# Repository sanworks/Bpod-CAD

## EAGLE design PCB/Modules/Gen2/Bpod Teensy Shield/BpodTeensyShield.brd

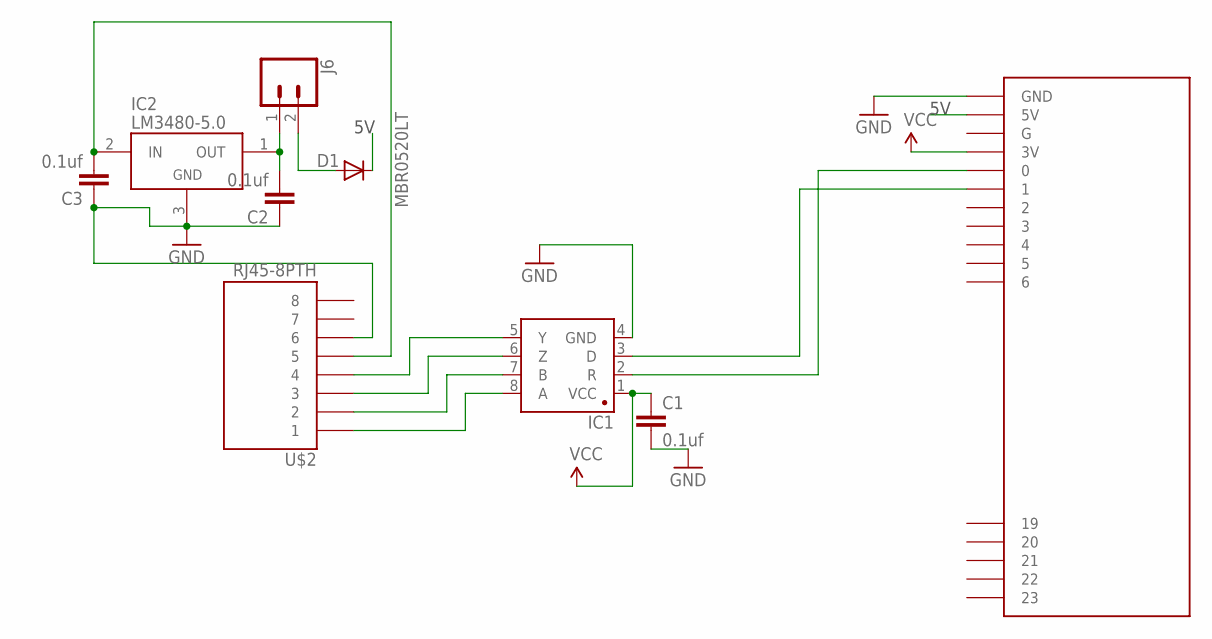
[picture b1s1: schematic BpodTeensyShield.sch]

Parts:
C1, C2, C3: 0.1uf; 1206@1
D1: MBR0520LT; SOD123
IC1: SN65HVD31DR; SO08
IC2: LM3480-5.0; SOT-23-3
J6: CONN_02; 1X02
U$1: AUDIOSHIELD
U$2: RJ45-8PTH; RJ45-8

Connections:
5V: D1.C, U$1.5V
GND: C1.2, C2.1, C3.1, IC1.4 (GND), IC2.3 (GND), U$1.GND, U$2.6
unnamed: IC1.8 (A), U$2.1
unnamed: IC1.7 (B), U$2.2
unnamed: IC1.6 (Z), U$2.3
unnamed: IC1.5 (Y), U$2.4
unnamed: C2.2, IC2.1 (OUT), J6.1
unnamed: D1.A, J6.2
unnamed: C3.2, IC2.2 (IN), U$2.5
RX1: IC1.2 (R), U$1.0
TX1: IC1.3 (D), U$1.1
VCC: C1.1, IC1.1 (VCC), U$1.3V

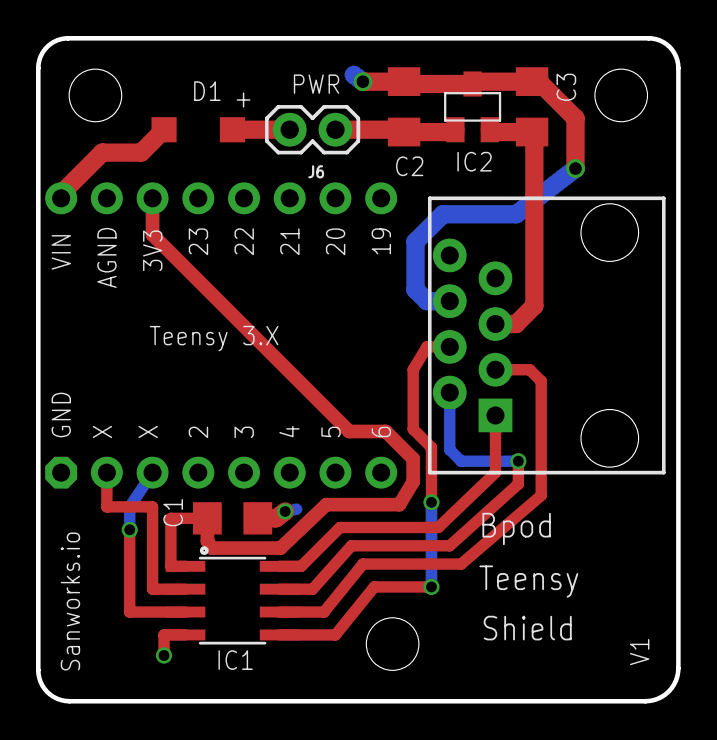
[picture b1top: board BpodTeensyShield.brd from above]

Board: 2 copper layers, 35.6 x 36.8 mm, 9 parts (0 on the bottom side), 12 nets.

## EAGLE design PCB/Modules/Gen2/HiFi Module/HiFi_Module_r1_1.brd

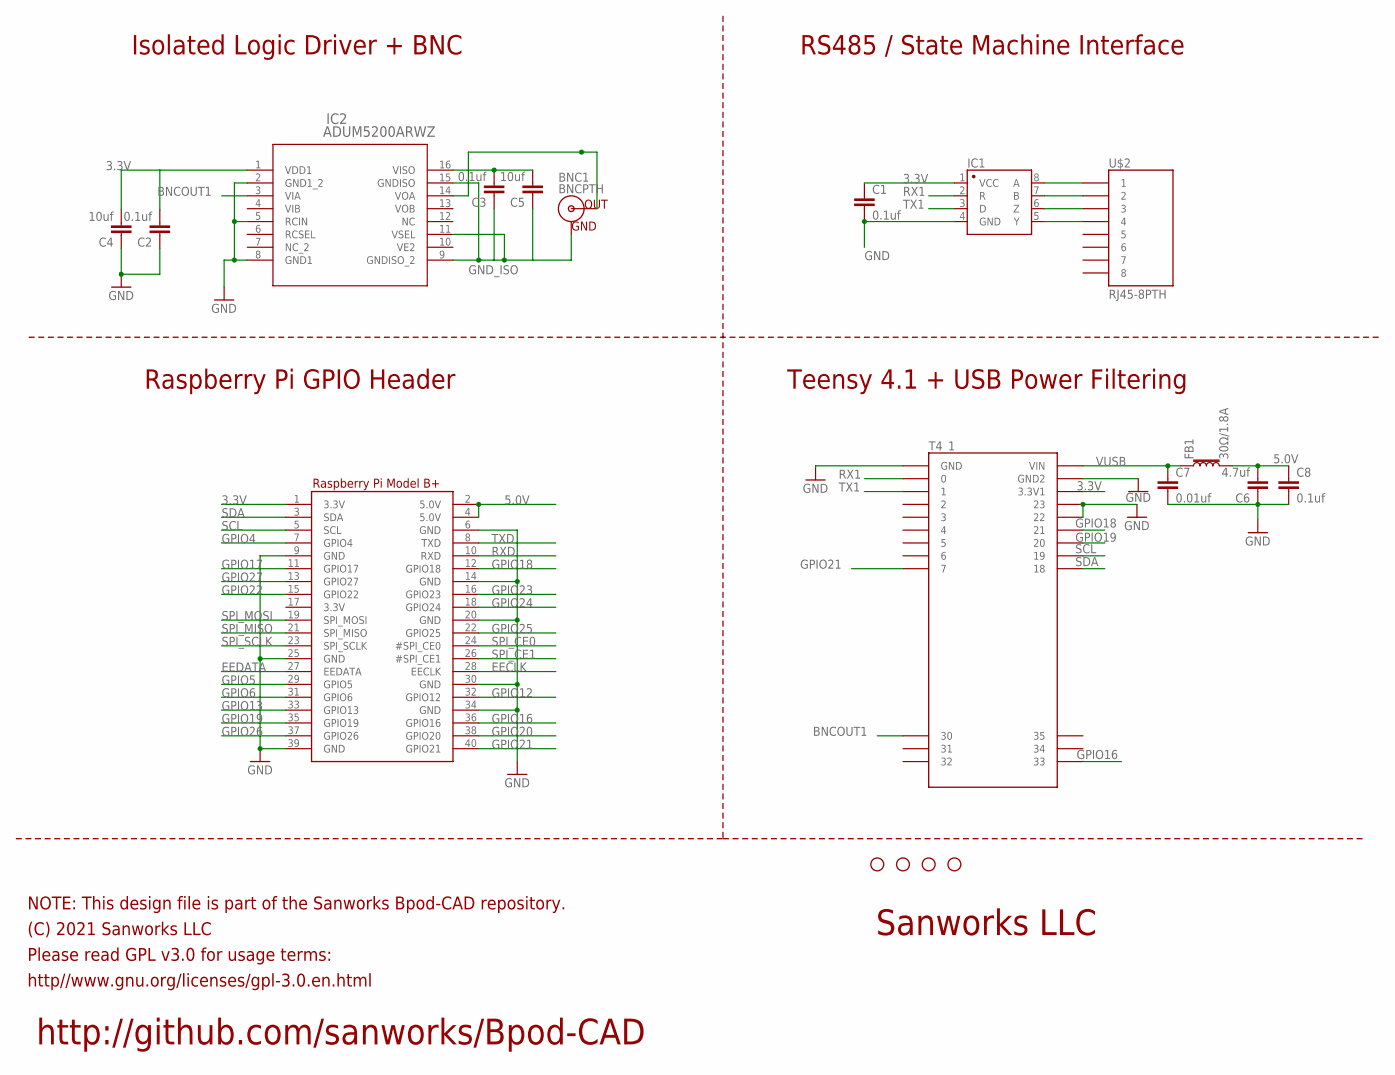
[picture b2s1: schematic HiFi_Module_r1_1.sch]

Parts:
BNC1: BNCPTH; BNC
C1, C2, C3, C8: 0.1uf; 0805
C4, C5: 10uf; 1206@2
C6: 4.7uf; 1206@2
C7: 0.01uf; 0805
FB1: 30Ω/1.8A; 0603
H1, H2, H3, H4: STAND-OFF
IC1: SN65HVD31DR; SO08
IC2: ADUM5200ARWZ; RW_16
RPI1: RASPBERRYPI_BPLUS_IDC; 2X20
T4_1: TEENSY4.1_FORAUDIO
U$2: RJ45-8PTH; RJ45-8

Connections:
3.3V: C1.1, C2.2, C4.2, IC1.1 (VCC), IC2.1 (VDD1), RPI1.1 (3.3V), T4_1.3V3_LO (3.3V1)
5.0V: C6.2, C8.1, FB1.2, RPI1.2 (5.0V), RPI1.4 (5.0V)
BNCOUT1: IC2.3 (VIA), T4_1.30
EECLK: RPI1.28 (EECLK)
EEDATA: RPI1.27 (EEDATA)
GND: C1.2, C2.1, C4.1, C6.1, C7.2, C8.2, IC1.4 (GND), IC2.2 (GND1_2), IC2.5 (RCIN), IC2.8 (GND1), RPI1.6 (GND), RPI1.9 (GND), RPI1.14 (GND), RPI1.20 (GND), RPI1.25 (GND), RPI1.30 (GND), RPI1.34 (GND), RPI1.39 (GND), T4_1.22/A8 (22), T4_1.23/A9 (23), T4_1.AGND (GND), T4_1.GND (GND2)
GND_ISO: BNC1.GND, C3.1, C5.1, IC2.9 (GNDISO_2), IC2.11 (VSEL), IC2.15 (GNDISO)
GPIO4: RPI1.7 (GPIO4)
GPIO5: RPI1.29 (GPIO5)
GPIO6: RPI1.31 (GPIO6)
GPIO12: RPI1.32 (GPIO12)
GPIO13: RPI1.33 (GPIO13)
GPIO16: RPI1.36 (GPIO16), T4_1.33
GPIO17: RPI1.11 (GPIO17)
GPIO18: RPI1.12 (GPIO18), T4_1.21/A7 (21)
GPIO19: RPI1.35 (GPIO19), T4_1.20/A6 (20)
GPIO20: RPI1.38 (GPIO20)
GPIO21: RPI1.40 (GPIO21), T4_1.7
GPIO22: RPI1.15 (GPIO22)
GPIO23: RPI1.16 (GPIO23)
GPIO24: RPI1.18 (GPIO24)
GPIO25: RPI1.22 (GPIO25)
GPIO26: RPI1.37 (GPIO26)
GPIO27: RPI1.13 (GPIO27)
unnamed: IC1.6 (Z), U$2.3
unnamed: IC1.8 (A), U$2.1
unnamed: IC1.5 (Y), U$2.4
unnamed: IC1.7 (B), U$2.2
unnamed: C3.2, C5.2, IC2.16 (VISO)
unnamed: BNC1.S (OUT), IC2.14 (VOA)
RX1: IC1.2 (R), T4_1.0/RX (0)
RXD: RPI1.10 (RXD)
SCL: RPI1.5 (SCL), T4_1.19/A5/SCL (19)
SDA: RPI1.3 (SDA), T4_1.18/A4/SDA (18)
SPI_CE0: RPI1.24 (#SPI_CE0)
SPI_CE1: RPI1.26 (#SPI_CE1)
SPI_MISO: RPI1.21 (SPI_MISO)
SPI_MOSI: RPI1.19 (SPI_MOSI)
SPI_SCLK: RPI1.23 (SPI_SCLK)
TX1: IC1.3 (D), T4_1.1/TX (1)
TXD: RPI1.8 (TXD)
VUSB: C7.1, FB1.1, T4_1.VIN

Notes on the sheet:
http://github.com/sanworks/Bpod-CAD
NOTE: This design file is part of the Sanworks Bpod-CAD repository.
(C) 2021 Sanworks LLC
http//www.gnu.org/licenses/gpl-3.0.en.html
Please read GPL v3.0 for usage terms:
Sanworks LLC
Isolated Logic Driver + BNC
RS485 / State Machine Interface
Raspberry Pi GPIO Header
Teensy 4.1 + USB Power Filtering

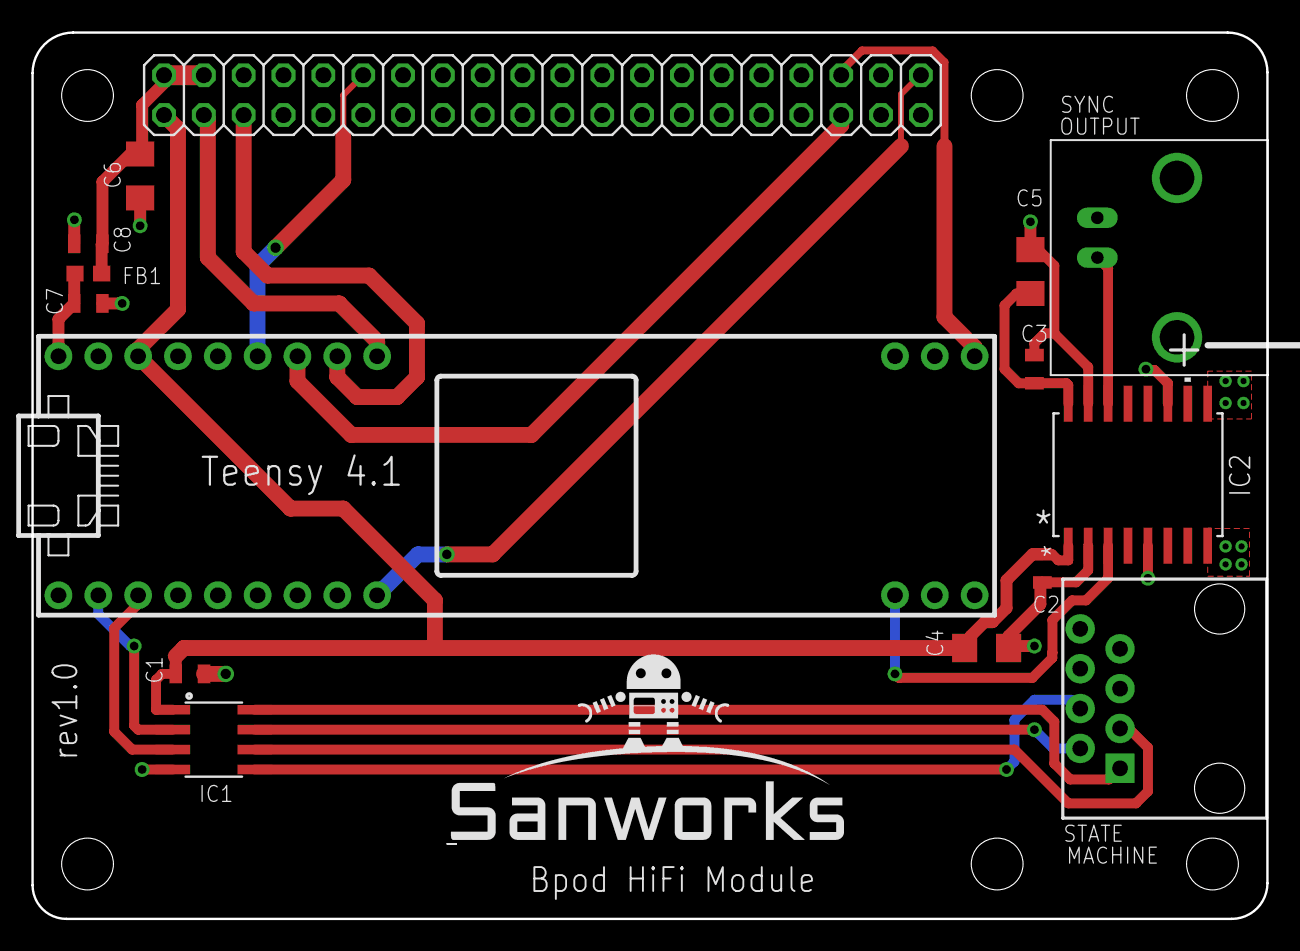
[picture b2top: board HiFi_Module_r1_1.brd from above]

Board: 2 copper layers, 78.7 x 56.5 mm, 22 parts (0 on the bottom side), 20 nets.

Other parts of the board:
H5, H6: STAND-OFF
U$1: SANWORKS_LOGO

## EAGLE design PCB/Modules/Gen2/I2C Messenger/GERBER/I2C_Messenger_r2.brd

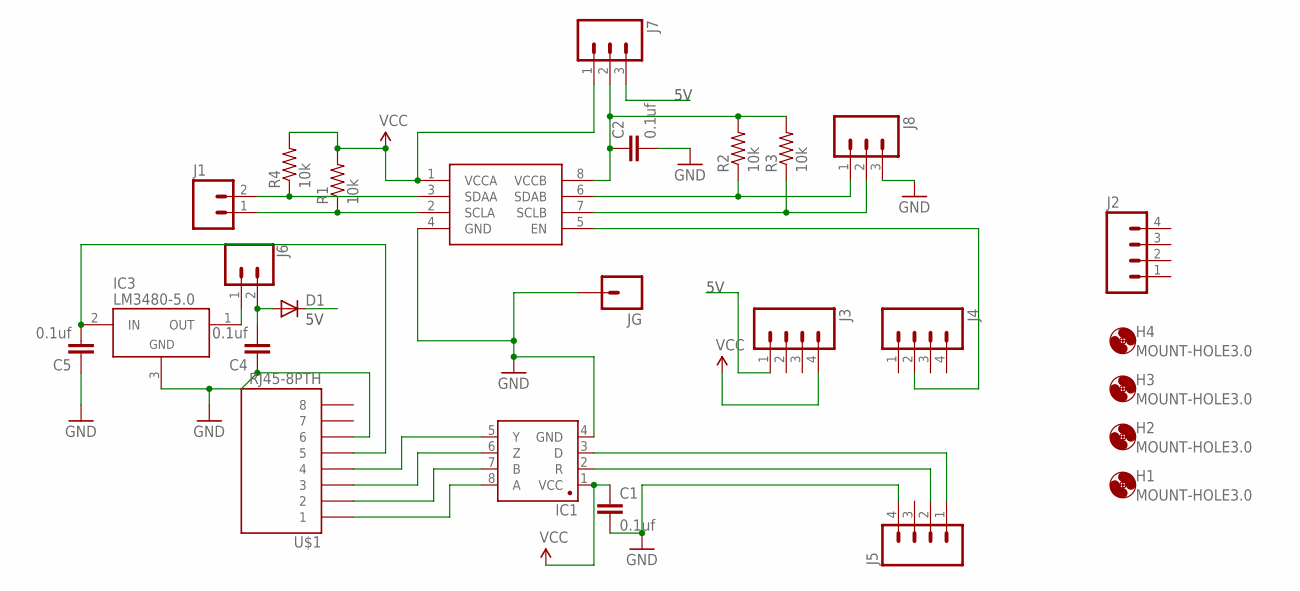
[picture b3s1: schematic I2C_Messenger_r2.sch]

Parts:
C1, C2, C4, C5: 0.1uf; 1206
D1: MBR0520LT; SOD123
H1, H2, H3, H4: MOUNT-HOLE3.0; 3,0
IC1: SN65HVD31DR; SO08
IC2: PCA9517; SO-08
IC3: LM3480-5.0; SOT-23-3
J1: M02PTH; 1X02@1
J2, J3, J4, J5: M04PTH; 1X04
J6: CONN_02; 1X02
J7: M03PTH; 1X03
J8: M03SCREW_LOCK; SCREWTERMINAL-3.5MM-3_LOCK.007S
JG: M01PTH; 1X01
R1, R2, R3, R4: 10k; 1206
U$1: RJ45-8PTH; RJ45-8

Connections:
5V: D1.C, J3.1, J7.3
GND: C1.2, C2.2, C4.1, C5.1, IC1.4 (GND), IC2.4 (GND), IC3.3 (GND), J5.4, J8.3, JG.1, U$1.6
unnamed: C4.2, D1.A, J6.2
unnamed: IC3.1 (OUT), J6.1
unnamed: IC1.3 (D), J5.1
unnamed: IC2.2 (SCLA), J1.1, R1.1
unnamed: IC1.2 (R), J5.2
unnamed: IC1.8 (A), U$1.1
unnamed: IC1.7 (B), U$1.2
unnamed: IC1.6 (Z), U$1.3
unnamed: IC1.5 (Y), U$1.4
unnamed: IC2.3 (SDAA), J1.2, R4.1
unnamed: C2.1, IC2.8 (VCCB), J7.2, R2.2, R3.2
unnamed: IC2.5 (EN), J4.2
unnamed: IC2.6 (SDAB), J8.1, R2.1
unnamed: IC2.7 (SCLB), J8.2, R3.1
unnamed: C5.2, IC3.2 (IN), U$1.5
VCC: C1.1, IC1.1 (VCC), IC2.1 (VCCA), J3.4, J7.1, R1.2, R4.2

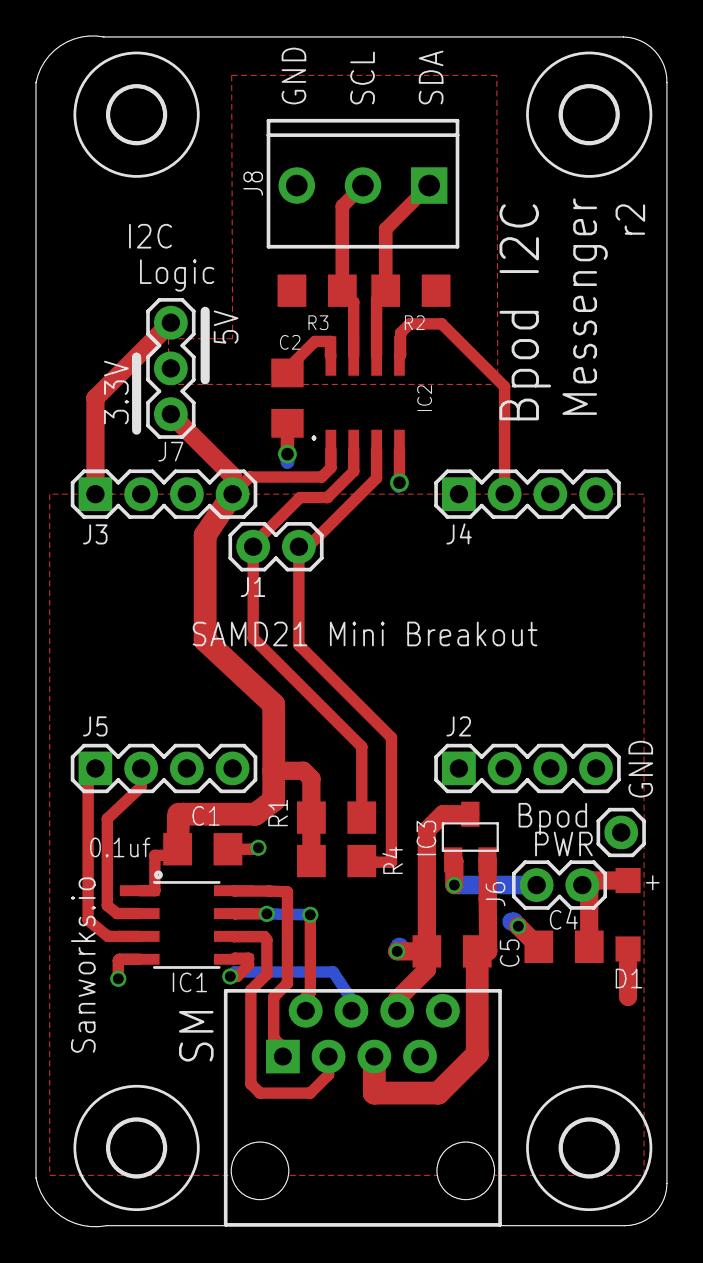
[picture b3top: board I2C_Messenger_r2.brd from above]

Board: 2 copper layers, 35.1 x 66.1 mm, 26 parts (0 on the bottom side), 18 nets.

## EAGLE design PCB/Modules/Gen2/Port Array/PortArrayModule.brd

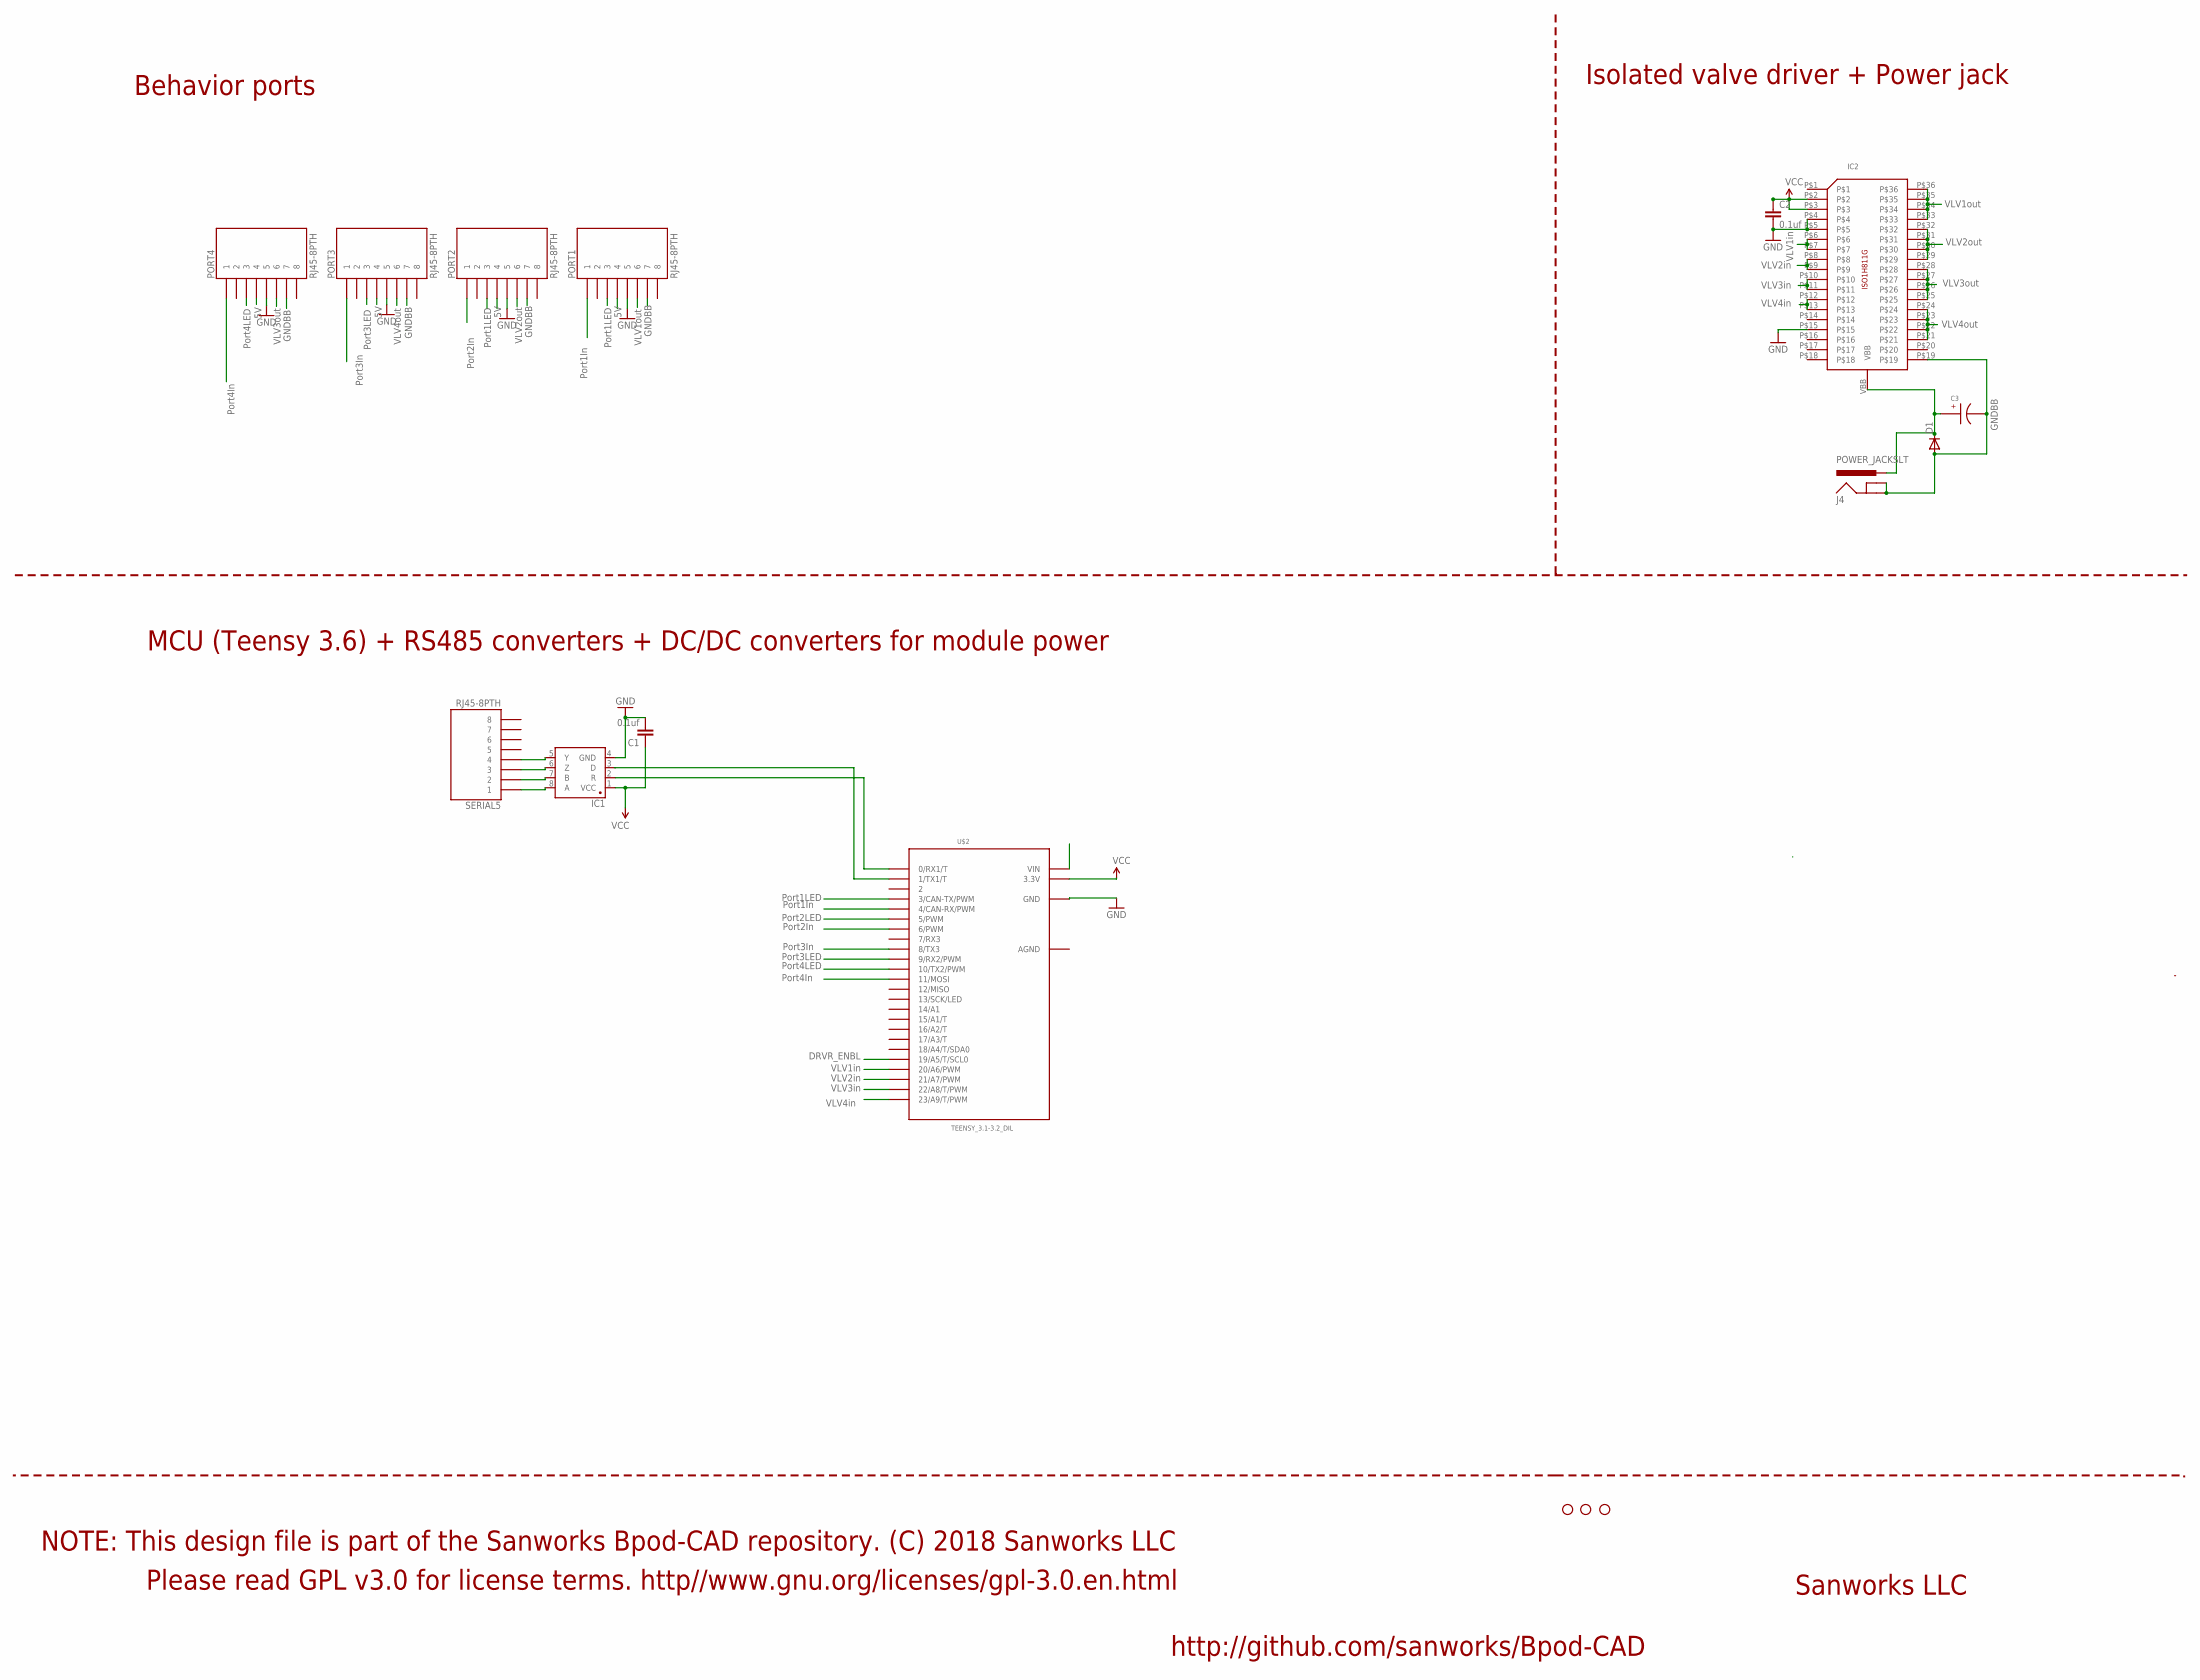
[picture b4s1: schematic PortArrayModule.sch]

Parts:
C1, C2: 0.1uf; 1206@1
C3: EEE-FK1H100UR
D1: DIODE-DO214AA; DO214AA
IC1: SN65HVD31DR; SO08
IC2: ISO1H811G
J4: POWER_JACKSLT; POWER_JACK_SLOT
JP3, JP4, JP5: STAND-OFF
PORT1, PORT2, PORT3, PORT4: RJ45-8PTH; RJ45-8
SERIAL5: RJ45-8PTH; RJ45-8
U$2: TEENSY_3.1-3.2_DIL; TEENSY_3.0-3.2&LC_DIL

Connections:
5V: PORT1.4, PORT2.4, PORT3.4, PORT4.4, U$2.VIN
AGND: U$2.AGND
DRVR_ENBL: U$2.19/A5 (19/A5/T/SCL0)
GND: C1.2, C2.2, IC1.4 (GND), IC2.P$4, IC2.P$5, IC2.P$15, PORT1.5, PORT2.5, PORT3.5, PORT4.5, U$2.GND
GNDBB: C3.CATHODE, D1.A, IC2.P$19, J4.GND@1 (GNDBREAK), J4.GND@2 (GND), PORT1.7, PORT2.7, PORT3.7, PORT4.7
unnamed: IC1.8 (A), SERIAL5.1
unnamed: IC1.7 (B), SERIAL5.2
unnamed: IC1.6 (Z), SERIAL5.3
unnamed: IC1.5 (Y), SERIAL5.4
unnamed: IC1.3 (D), U$2.1 (1/TX1/T)
unnamed: IC1.2 (R), U$2.0 (0/RX1/T)
PORT1IN: PORT1.1, U$2.4 (4/CAN-RX/PWM)
PORT1LED: PORT1.3, U$2.3 (3/CAN-TX/PWM)
PORT2IN: PORT2.1, U$2.6 (6/PWM)
PORT2LED: PORT2.3, U$2.5 (5/PWM)
PORT3IN: PORT3.1, U$2.8 (8/TX3)
PORT3LED: PORT3.3, U$2.9 (9/RX2/PWM)
PORT4IN: PORT4.1, U$2.11 (11/MOSI)
PORT4LED: PORT4.3, U$2.10 (10/TX2/PWM)
VBB: C3.ANODE, D1.C, IC2.VBB, J4.PWR
VCC: C1.1, C2.1, IC1.1 (VCC), IC2.P$2, IC2.P$3, U$2.3.3V
VLV1IN: IC2.P$6, IC2.P$7, U$2.20/A6 (20/A6/PWM)
VLV1OUT: IC2.P$33, IC2.P$34, IC2.P$35, IC2.P$36, PORT1.6
VLV2IN: IC2.P$8, IC2.P$9, U$2.21/A7 (21/A7/PWM)
VLV2OUT: IC2.P$29, IC2.P$30, IC2.P$31, IC2.P$32, PORT2.6
VLV3IN: IC2.P$12, IC2.P$13, U$2.23/A9 (23/A9/T/PWM)
VLV3OUT: IC2.P$21, IC2.P$22, IC2.P$23, IC2.P$24, PORT3.6
VLV4IN: IC2.P$10, IC2.P$11, U$2.22/A8 (22/A8/T/PWM)
VLV4OUT: IC2.P$25, IC2.P$26, IC2.P$27, IC2.P$28, PORT4.6

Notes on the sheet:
Port1In
Port2In
Port3In
Port4In
Port1LED
Port2LED
Port3LED
Port4LED
DRVR_ENBL
VLV2in
VLV3in
VLV4in
VLV1in
GNDBB
VLV1out
VLV2out
VLV3out
VLV4out
Sanworks LLC
http://github.com/sanworks/Bpod-CAD
Please read GPL v3.0 for license terms. http//www.gnu.org/licenses/gpl-3.0.en.html
NOTE: This design file is part of the Sanworks Bpod-CAD repository. (C) 2018 Sanworks LLC
Behavior ports
Isolated valve driver + Power jack
MCU (Teensy 3.6) + RS485 converters + DC/DC converters for module power

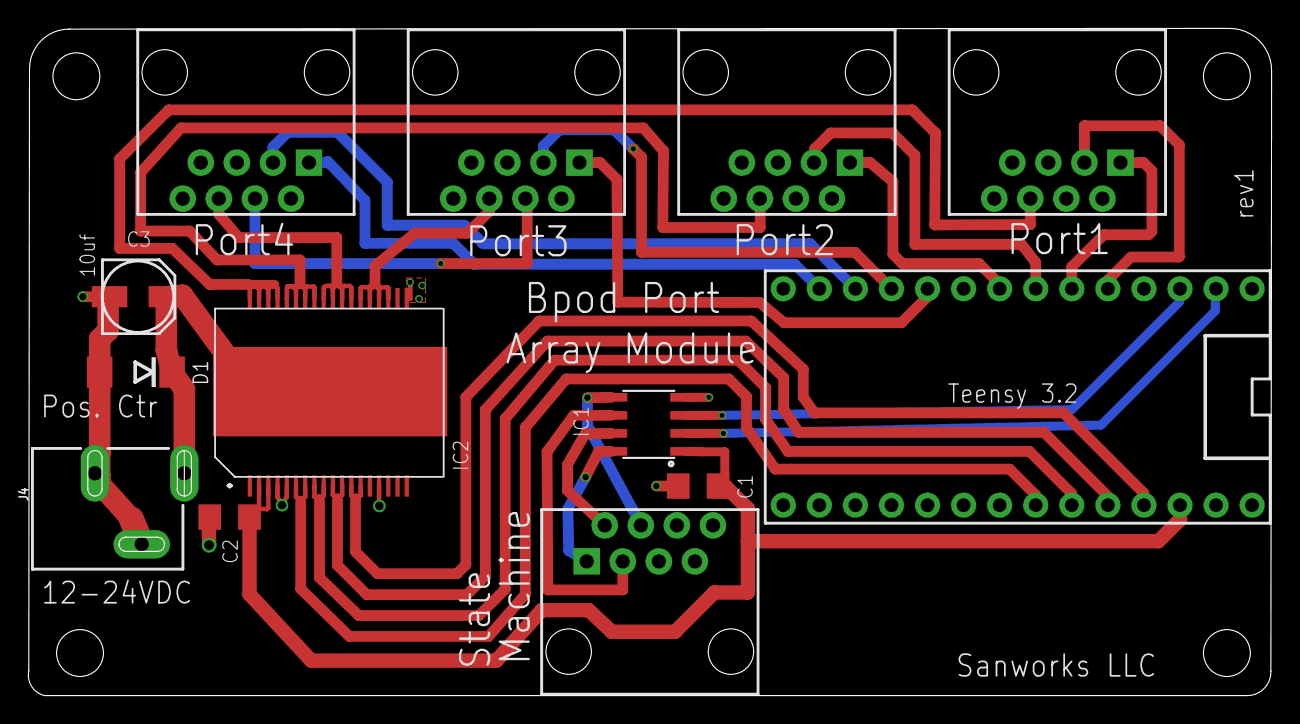
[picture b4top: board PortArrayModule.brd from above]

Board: 4 copper layers, 87.6 x 47.0 mm, 17 parts (0 on the bottom side), 27 nets.

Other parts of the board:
JP1: STAND-OFF

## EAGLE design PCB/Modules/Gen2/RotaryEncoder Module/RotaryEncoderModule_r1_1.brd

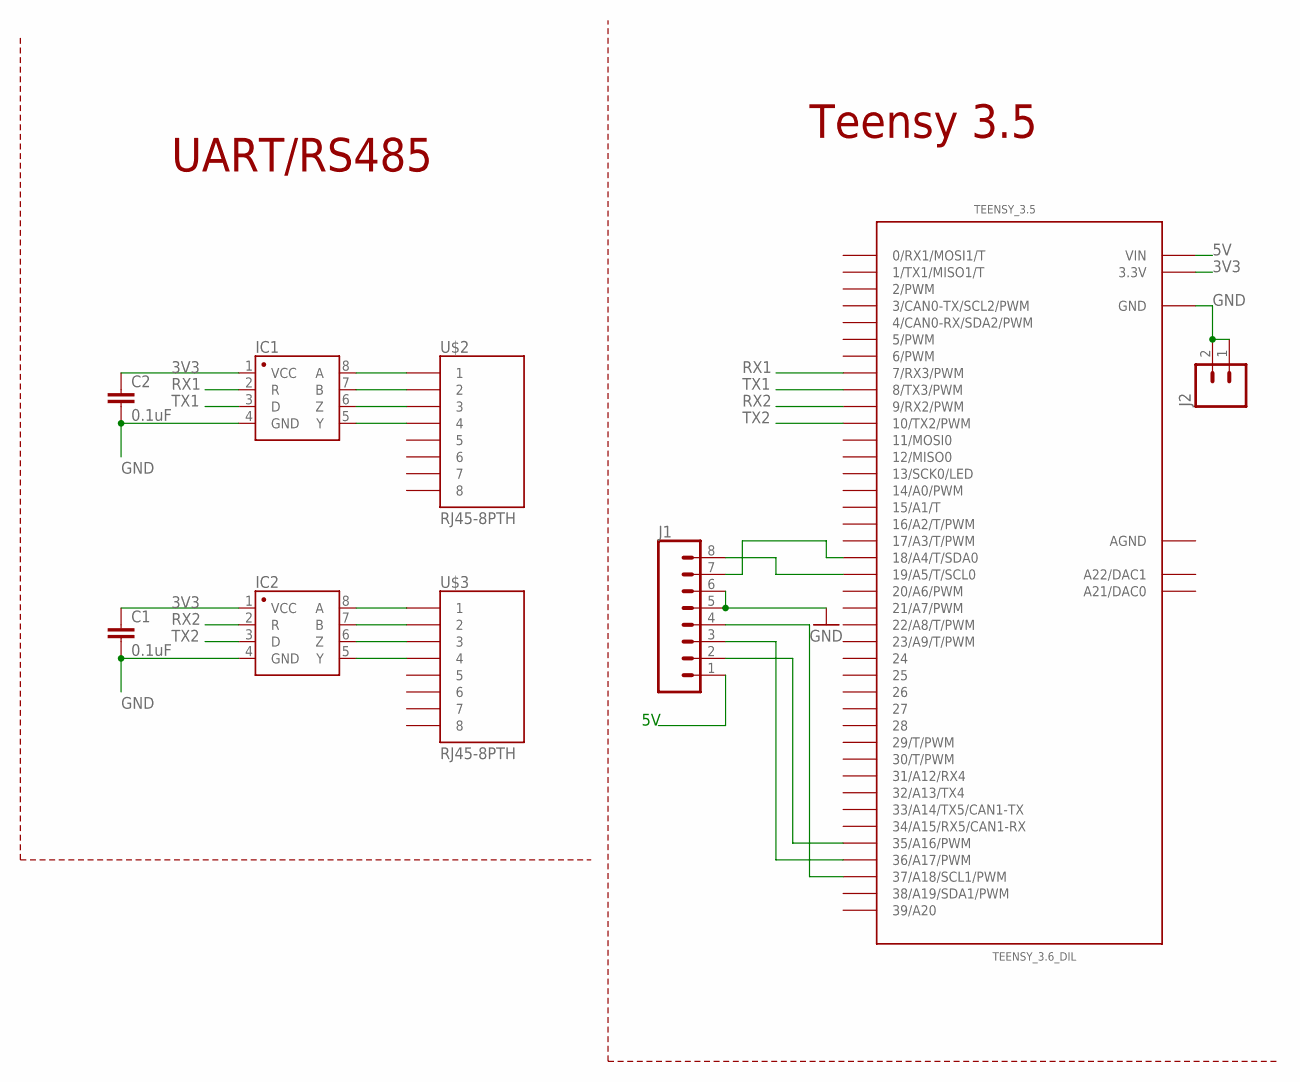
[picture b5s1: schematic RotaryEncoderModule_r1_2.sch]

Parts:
C1, C2: 0.1uF; 1206
IC1, IC2: SN65HVD31DR; SO08
J1: CONN_083.5MM-8; SCREWTERMINAL-3.5MM-8
J2: M023.5MM; SCREWTERMINAL-3.5MM-2
TEENSY_3.5: TEENSY_3.6_DIL
U$2, U$3: RJ45-8PTH; RJ45-8

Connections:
3V3: C1.1, C2.1, IC1.1 (VCC), IC2.1 (VCC), TEENSY_3.5.3.3V, TEENSY_3.5.3.3V3 (3.3V)
5V: J1.1, TEENSY_3.5.VIN
AGND: TEENSY_3.5.AGND
GND: C1.2, C2.2, IC1.4 (GND), IC2.4 (GND), J1.5, J1.6, J2.1, J2.2, TEENSY_3.5.GND, TEENSY_3.5.GND1 (GND)
unnamed: IC1.6 (Z), U$2.3
unnamed: IC1.8 (A), U$2.1
unnamed: IC1.5 (Y), U$2.4
unnamed: IC1.7 (B), U$2.2
unnamed: IC2.6 (Z), U$3.3
unnamed: IC2.5 (Y), U$3.4
unnamed: IC2.8 (A), U$3.1
unnamed: IC2.7 (B), U$3.2
unnamed: J1.8, TEENSY_3.5.19/A5 (19/A5/T/SCL0)
unnamed: J1.7, TEENSY_3.5.18/A4 (18/A4/T/SDA0)
unnamed: J1.2, TEENSY_3.5.35/A16 (35/A16/PWM)
unnamed: J1.3, TEENSY_3.5.36/A17 (36/A17/PWM)
unnamed: J1.4, TEENSY_3.5.37/A18 (37/A18/SCL1/PWM)
RX1: IC1.2 (R), TEENSY_3.5.7 (7/RX3/PWM)
RX2: IC2.2 (R), TEENSY_3.5.9 (9/RX2/PWM)
TX1: IC1.3 (D), TEENSY_3.5.8 (8/TX3/PWM)
TX2: IC2.3 (D), TEENSY_3.5.10 (10/TX2/PWM)

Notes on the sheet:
Teensy 3.5
UART/RS485

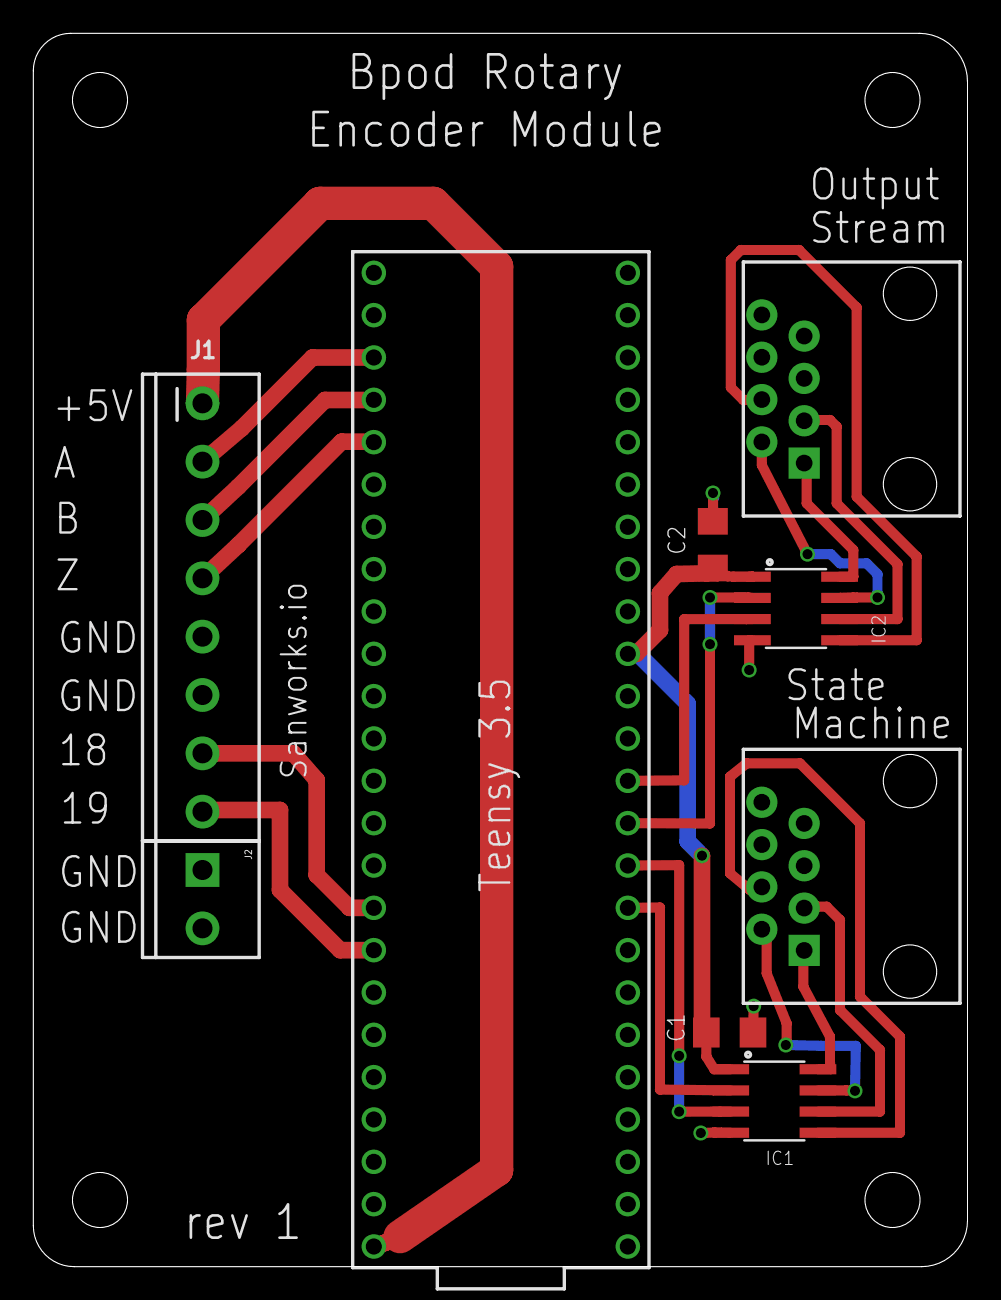
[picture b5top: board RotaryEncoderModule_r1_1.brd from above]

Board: 2 copper layers, 56.0 x 74.0 mm, 13 parts (0 on the bottom side), 20 nets.

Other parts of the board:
U$5, U$6, U$7, U$8: STAND-OFF

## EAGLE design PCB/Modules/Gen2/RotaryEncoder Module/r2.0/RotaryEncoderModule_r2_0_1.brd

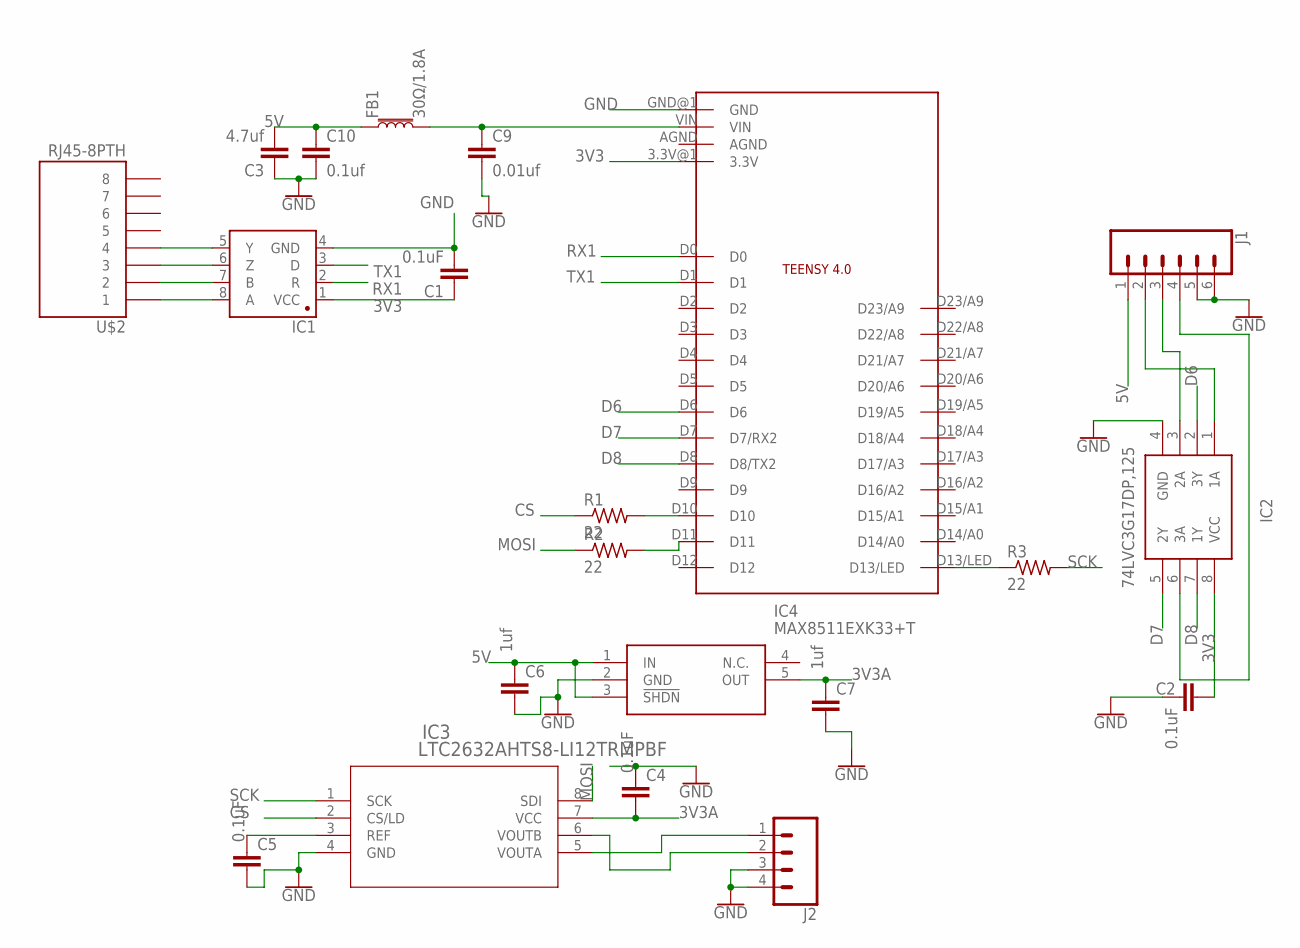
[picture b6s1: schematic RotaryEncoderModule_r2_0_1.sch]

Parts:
C1, C2, C4, C5: 0.1uF; 0805
C3: 4.7uf; 1206@2
C6, C7: 1uf; 0805
C9: 0.01uf; 0805
C10: 0.1uf; 0805
FB1: 30Ω/1.8A; 0603
IC1: SN65HVD31DR; SO08
IC2: 74LVC3G17DP,125; SOP65P400X110-8N
IC3: LTC2632AHTS8-LI12TRMPBF; TSOT-23-8_1P625X2P9_ADI
IC4: MAX8511EXK33+T; SOT65P210X110-5N
J1: CONN_063.5MM-6; SCREWTERMINAL-3.5MM-6
J2: CONN_04SCREW_LOCK; SCREWTERMINAL-3.5MM-4_LOCK
MC1: TEENSY4.0_SIMPLE_NO_VUSB
R1, R2, R3: 22; R0805
U$2: RJ45-8PTH; RJ45-8

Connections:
3V3: C1.1, C2.1, IC1.1 (VCC), IC2.8 (VCC), MC1.3.3V@1 (3.3V)
3V3A: C4.2, C7.1, IC3.7 (VCC), IC4.5 (OUT)
5V: C3.2, C6.1, C10.1, FB1.1, IC4.1 (IN), IC4.3 (!SHDN), J1.1
CS: IC3.2 (CS/LD), R1.1
D6: IC2.2 (3Y), MC1.D6
D7: IC2.5 (2Y), MC1.D7 (D7/RX2)
D8: IC2.7 (1Y), MC1.D8 (D8/TX2)
GND: C1.2, C2.2, C3.1, C4.1, C5.2, C6.2, C7.2, C9.2, C10.2, IC1.4 (GND), IC2.4 (GND), IC3.4 (GND), IC4.2 (GND), J1.5, J1.6, J2.3, J2.4, MC1.GND@1 (GND)
MOSI: IC3.8 (SDI), R2.1
unnamed: IC1.6 (Z), U$2.3
unnamed: IC2.1 (1A), J1.2
unnamed: IC1.8 (A), U$2.1
unnamed: IC1.5 (Y), U$2.4
unnamed: IC1.7 (B), U$2.2
unnamed: IC2.3 (2A), J1.3
unnamed: IC2.6 (3A), J1.4
unnamed: IC3.5 (VOUTA), J2.1
unnamed: IC3.6 (VOUTB), J2.2
unnamed: C5.1, IC3.3 (REF)
unnamed: MC1.D10, R1.2
unnamed: MC1.D11, R2.2
unnamed: MC1.D13/LED, R3.1
unnamed: C9.1, FB1.2, MC1.VIN
RX1: IC1.2 (R), MC1.D0
SCK: IC3.1 (SCK), R3.2
TX1: IC1.3 (D), MC1.D1

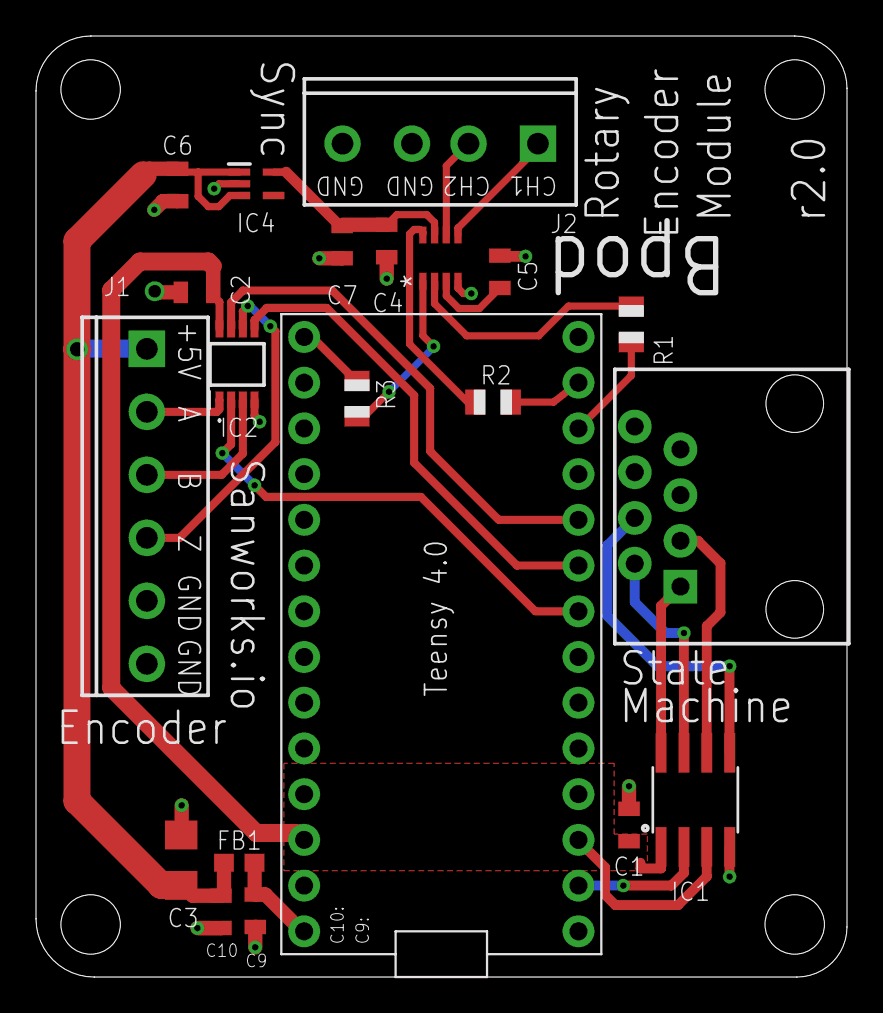
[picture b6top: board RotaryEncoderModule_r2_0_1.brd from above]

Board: 2 copper layers, 45.1 x 52.3 mm, 25 parts (0 on the bottom side), 26 nets.

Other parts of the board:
U$1, U$3, U$4, U$5: STAND-OFF

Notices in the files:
parts and their libraries:
SparkFun: Licensing: CC v3.0 Share-Alike You are welcome to use this library for commercial purposes.
SparkFun-Capacitors: Licensing: Creative Commons ShareAlike 4.0 International - https://creativecommons.org/licenses/by-sa/4.0
COPYRIGHT: Copyright (C) 2022 Ultra Librarian. All rights reserved.
